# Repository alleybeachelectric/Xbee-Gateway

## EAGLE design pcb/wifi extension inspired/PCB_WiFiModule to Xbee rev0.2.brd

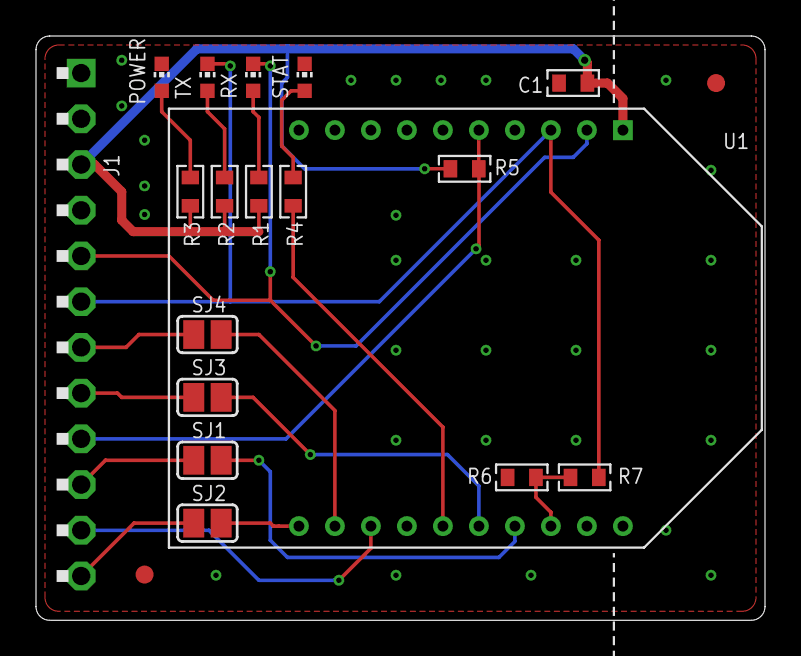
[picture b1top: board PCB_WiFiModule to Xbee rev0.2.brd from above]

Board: 2 copper layers, 40.5 x 32.5 mm, 20 parts (0 on the bottom side), 20 nets.

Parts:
C1: 10u/4V; 0603
F1, F2: REF
J1: FA12-1W
POWER: CHIP-LED0603
R1, R2, R3, R4: 1K; 0603
R5: 1M; 0603
R6: 100K; 0603
R7: 470K; 0603
RX: CHIP-LED0603
SJ1, SJ2, SJ3, SJ4: SJ
STAT: CHIP-LED0603
TX: CHIP-LED0603
U1: XBP9B-DMUT-002

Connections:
+3.3V: C1.1, J1.3, R1.2, R2.2, R3.2, R5.2, U1.1
/WF_RST: J1.9, R5.1, U1.5
DGND: C1.2, J1.1, J1.4, POWER.C, R6.1, STAT.C, U1.10
DIO5: R4.2, U1.15
unnamed: R4.1, STAT.A
unnamed: R1.1, RX.A
unnamed: R2.1, TX.A
unnamed: R6.2, R7.1, U1.18
unnamed: POWER.A, R3.1
unnamed: SJ4.2, U1.12
unnamed: SJ2.2, U1.11
unnamed: SJ3.2, U1.16
unnamed: SJ1.2, U1.17
RE0: J1.11, U1.13
RF1: J1.12, SJ2.1
U6RX: J1.5, RX.C, U1.2
U6TX: J1.6, R7.2, TX.C, U1.3
WF_CTS: J1.8, SJ3.1
WF_GP8: J1.10, SJ1.1
WF_RTS: J1.7, SJ4.1

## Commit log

2017-11-29 inital commit
2017-12-07 init
2017-12-09 rev0.1 routed
    used the wifi module for board dimensions and schematic reference. need the traces and components verified.
2017-12-09 cleaned up repo
2017-12-15 cleaned up routing, rerouted some SJ to go to different GPIO on the Xbee module.
2017-12-21 rev1.0 ready for review.
2017-12-21 rev1.0 ready for review
    cleaned up files and organized.

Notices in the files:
pcb/wifi extension inspired/PCB_WiFiModule to Xbee rev0.2.brd:
(C) 2014 eLock Technologies LLC
